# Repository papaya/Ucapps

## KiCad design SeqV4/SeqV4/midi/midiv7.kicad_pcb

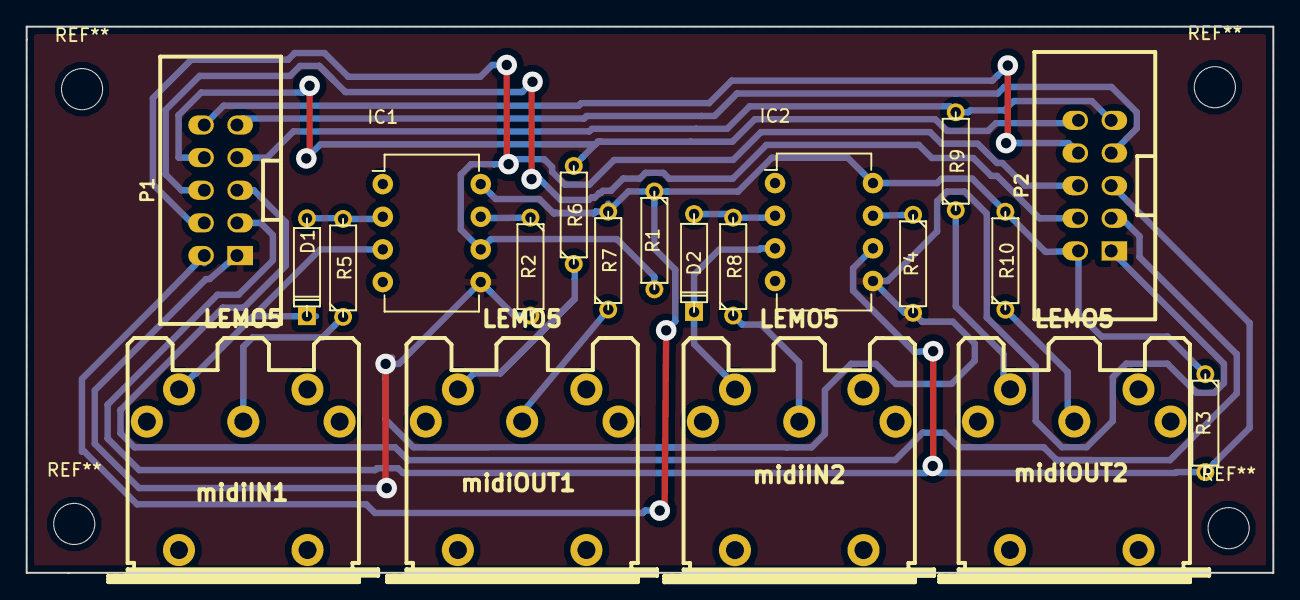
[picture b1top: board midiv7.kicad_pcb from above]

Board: 2 copper layers, 97.0 x 42.5 mm, 20 parts (0 on the bottom side), 22 nets.

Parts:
D1, D2: 1N4148; D3
IC1, IC2: 6N138; DIP-8_W7.62mm
P1, P2: CONN_02X05; vasch_strip_5x2
R1, R2, R3, R4, R5, R6, R7, R8, R9, R10: R; R3
midiIN1, midiIN2: LEMO5; din-5
midiOUT1, midiOUT2: LEMO5; din-5

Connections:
+5V: IC1.8, IC2.8, P1.2, P2.2, R1.1, R3.1, R7.2, R10.2
GND: IC1.5, IC2.5, P1.1, P2.1, R2.2, R4.2
unnamed: D1.1, IC1.3, midiIN1.5
unnamed: D1.2, IC1.2, R5.2
unnamed: D2.1, IC2.3, midiIN2.5
unnamed: D2.2, IC2.2, R8.2
unnamed: IC1.6, P1.4, P2.6, R1.2
unnamed: IC1.7, R2.1
unnamed: IC2.6, P1.3, P2.5, R3.2
unnamed: IC2.7, R4.1
unnamed: P1.5, P2.3
unnamed: P1.6, P2.4
unnamed: P1.7, P2.9, R9.2
unnamed: P1.8, P2.10, R6.2
unnamed: P1.9, P2.7
unnamed: P1.10, P2.8
unnamed: R5.1, midiIN1.2
unnamed: R6.1, midiOUT1.5
unnamed: R7.1, midiOUT1.2
unnamed: R8.1, midiIN2.2
unnamed: R9.1, midiOUT2.5
unnamed: R10.1, midiOUT2.2
